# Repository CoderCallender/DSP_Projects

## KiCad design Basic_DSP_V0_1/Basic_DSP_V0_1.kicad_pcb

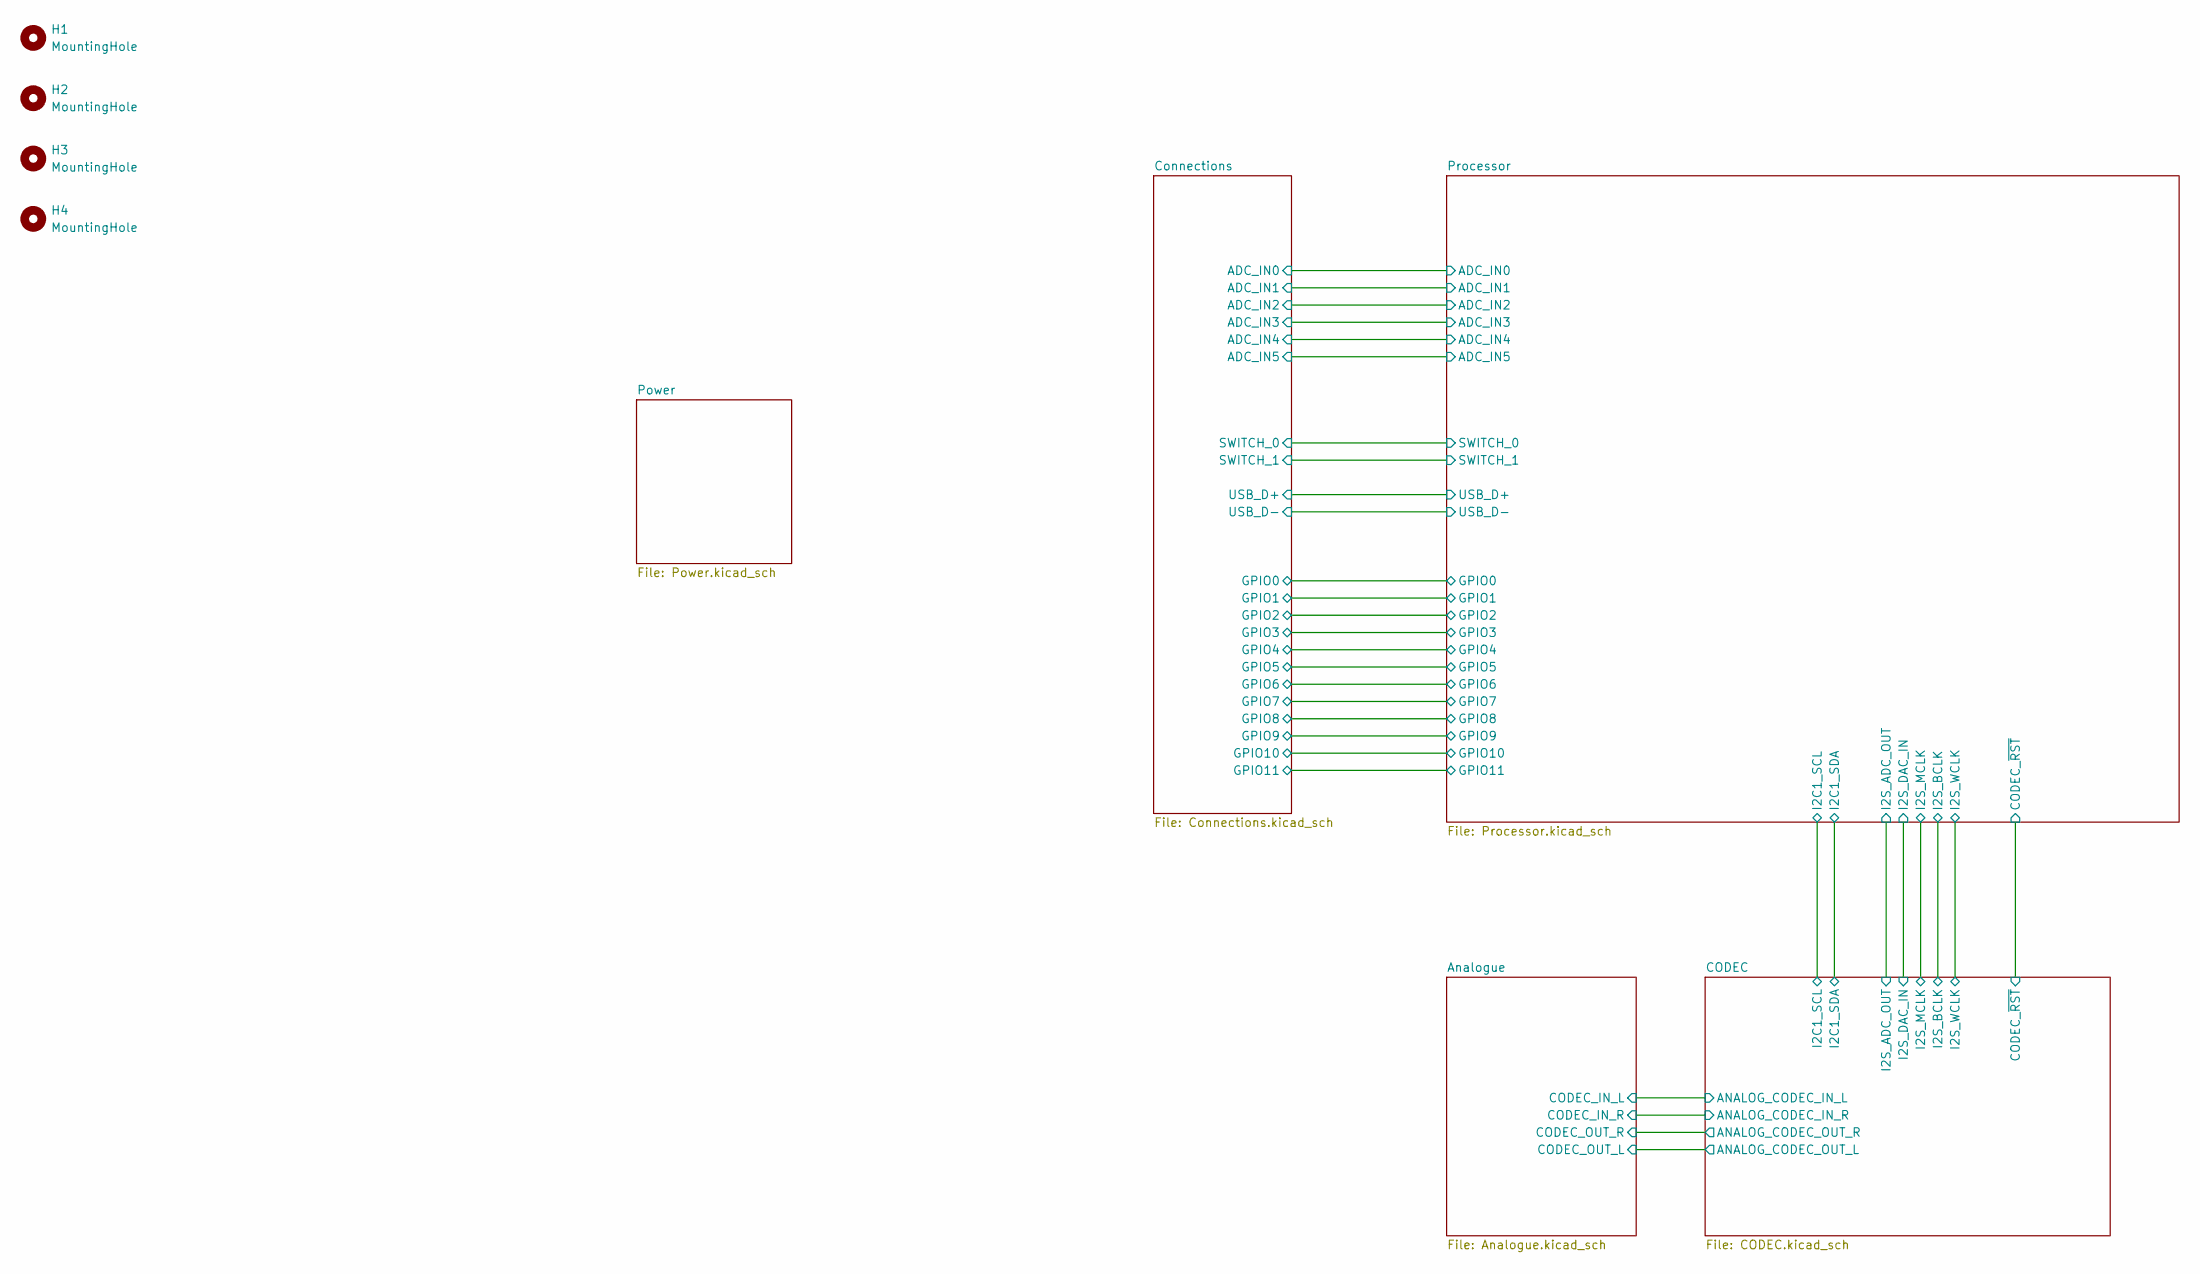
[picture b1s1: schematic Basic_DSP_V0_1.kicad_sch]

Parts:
H1, H2, H3, H4: MountingHole; MountingHole_3.2mm_M3_ISO7380_Pad

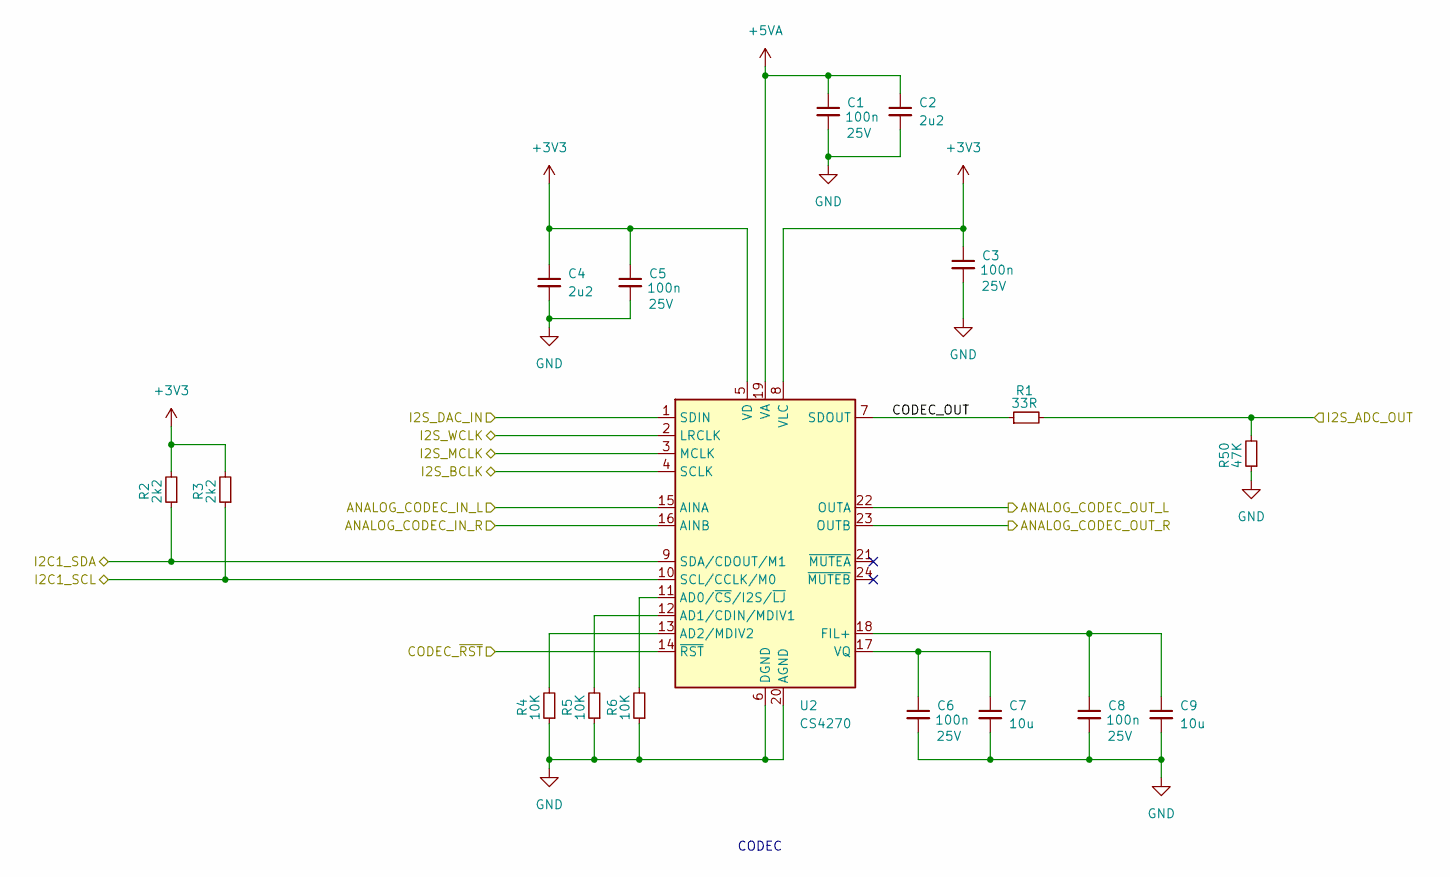
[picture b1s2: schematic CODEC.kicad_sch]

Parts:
C1, C3, C5, C6, C8: 100n; C_0603_1608Metric_Pad1.08x0.95mm_HandSolder; Voltage 25V; MPN 0603B104M250NT
C2, C4: 2u2; C_0603_1608Metric_Pad1.08x0.95mm_HandSolder; Voltage 25V; MPN 0603B225K250NT
C7, C9: 10u; C_0603_1608Metric_Pad1.08x0.95mm_HandSolder; Voltage 25V; MPN CL10A106MA8NRNC
R1: 33R; R_0603_1608Metric_Pad0.98x0.95mm_HandSolder; MPN WR06X33R0FTL
R2, R3: 2k2; R_0603_1608Metric_Pad0.98x0.95mm_HandSolder; MPN 0603WAF2201T5E
R4, R5, R6: 10K; R_0603_1608Metric_Pad0.98x0.95mm_HandSolder; MPN 0603WAF1002T5E
R50: 47K; R_0603_1608Metric_Pad0.98x0.95mm_HandSolder; MPN RC0603FR-0747KL
U2: CS4270; TSSOP-24_4.4x7.8mm_P0.65mm; MPN CS4270-CZZR

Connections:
+3V3: C3.1, C4.1, C5.1, R2.2, R3.2, U2.5 (VD), U2.8 (VLC); also elsewhere on the board
+5VA: C1.1, C2.1, U2.19 (VA); also elsewhere on the board
/Analogue/CODEC_IN_L: U2.15 (AINA); also elsewhere on the board
/Analogue/CODEC_IN_R: U2.16 (AINB); also elsewhere on the board
/Analogue/CODEC_OUT_L: U2.22 (OUTA); also elsewhere on the board
/Analogue/CODEC_OUT_R: U2.23 (OUTB); also elsewhere on the board
/CODEC/CODEC_OUT: R1.1, U2.7 (SDOUT)
/CODEC/CODEC_~RST: U2.14 (~RST); also elsewhere on the board
/CODEC/I2C1_SCL: R3.1, U2.10 (SCL/CCLK/M0); also elsewhere on the board
/CODEC/I2C1_SDA: R2.1, U2.9 (SDA/CDOUT/M1); also elsewhere on the board
/CODEC/I2S_ADC_OUT: R1.2, R50.2; also elsewhere on the board
/CODEC/I2S_BCLK: U2.4 (SCLK); also elsewhere on the board
/CODEC/I2S_DAC_IN: U2.1 (SDIN); also elsewhere on the board
/CODEC/I2S_MCLK: U2.3 (MCLK); also elsewhere on the board
/CODEC/I2S_WCLK: U2.2 (LRCLK); also elsewhere on the board
GND: C1.2, C2.2, C3.2, C4.2, C5.2, C6.2, C7.2, C8.2, C9.2, R4.1, R5.1, R6.1, R50.1, U2.6 (DGND), U2.20 (AGND); also elsewhere on the board
unnamed: R6.2, U2.11 (AD0/~CS/I2S/~LJ)
unnamed: R5.2, U2.12 (AD1/CDIN/MDIV1)
unnamed: R4.2, U2.13 (AD2/MDIV2)
unnamed: C8.1, C9.1, U2.18 (FIL+)
unnamed: C6.1, C7.1, U2.17 (VQ)

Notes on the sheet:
CODEC

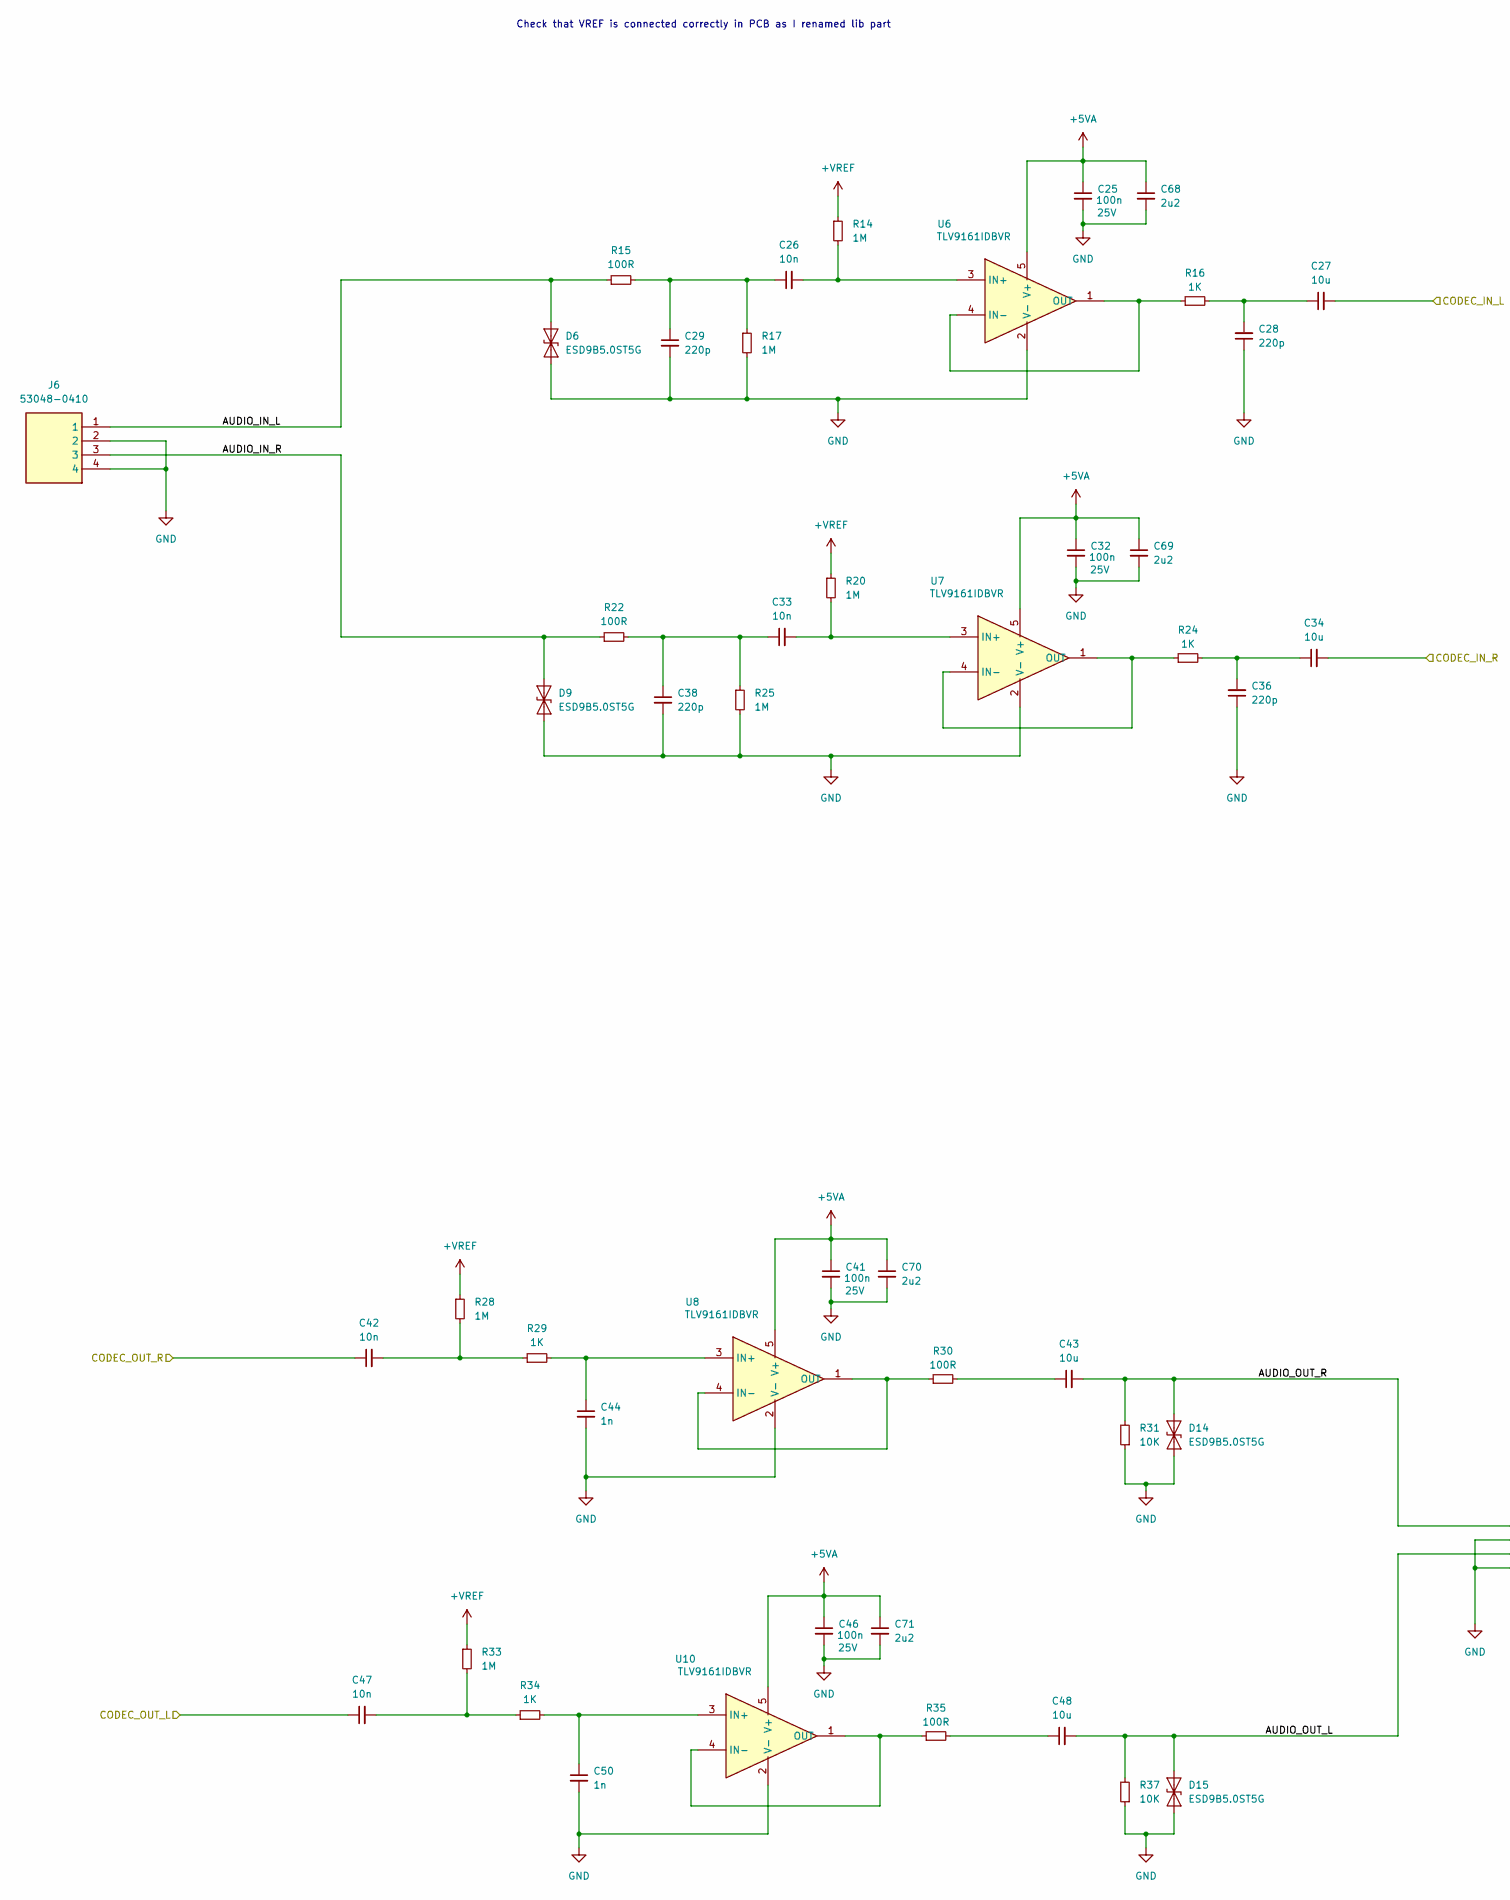
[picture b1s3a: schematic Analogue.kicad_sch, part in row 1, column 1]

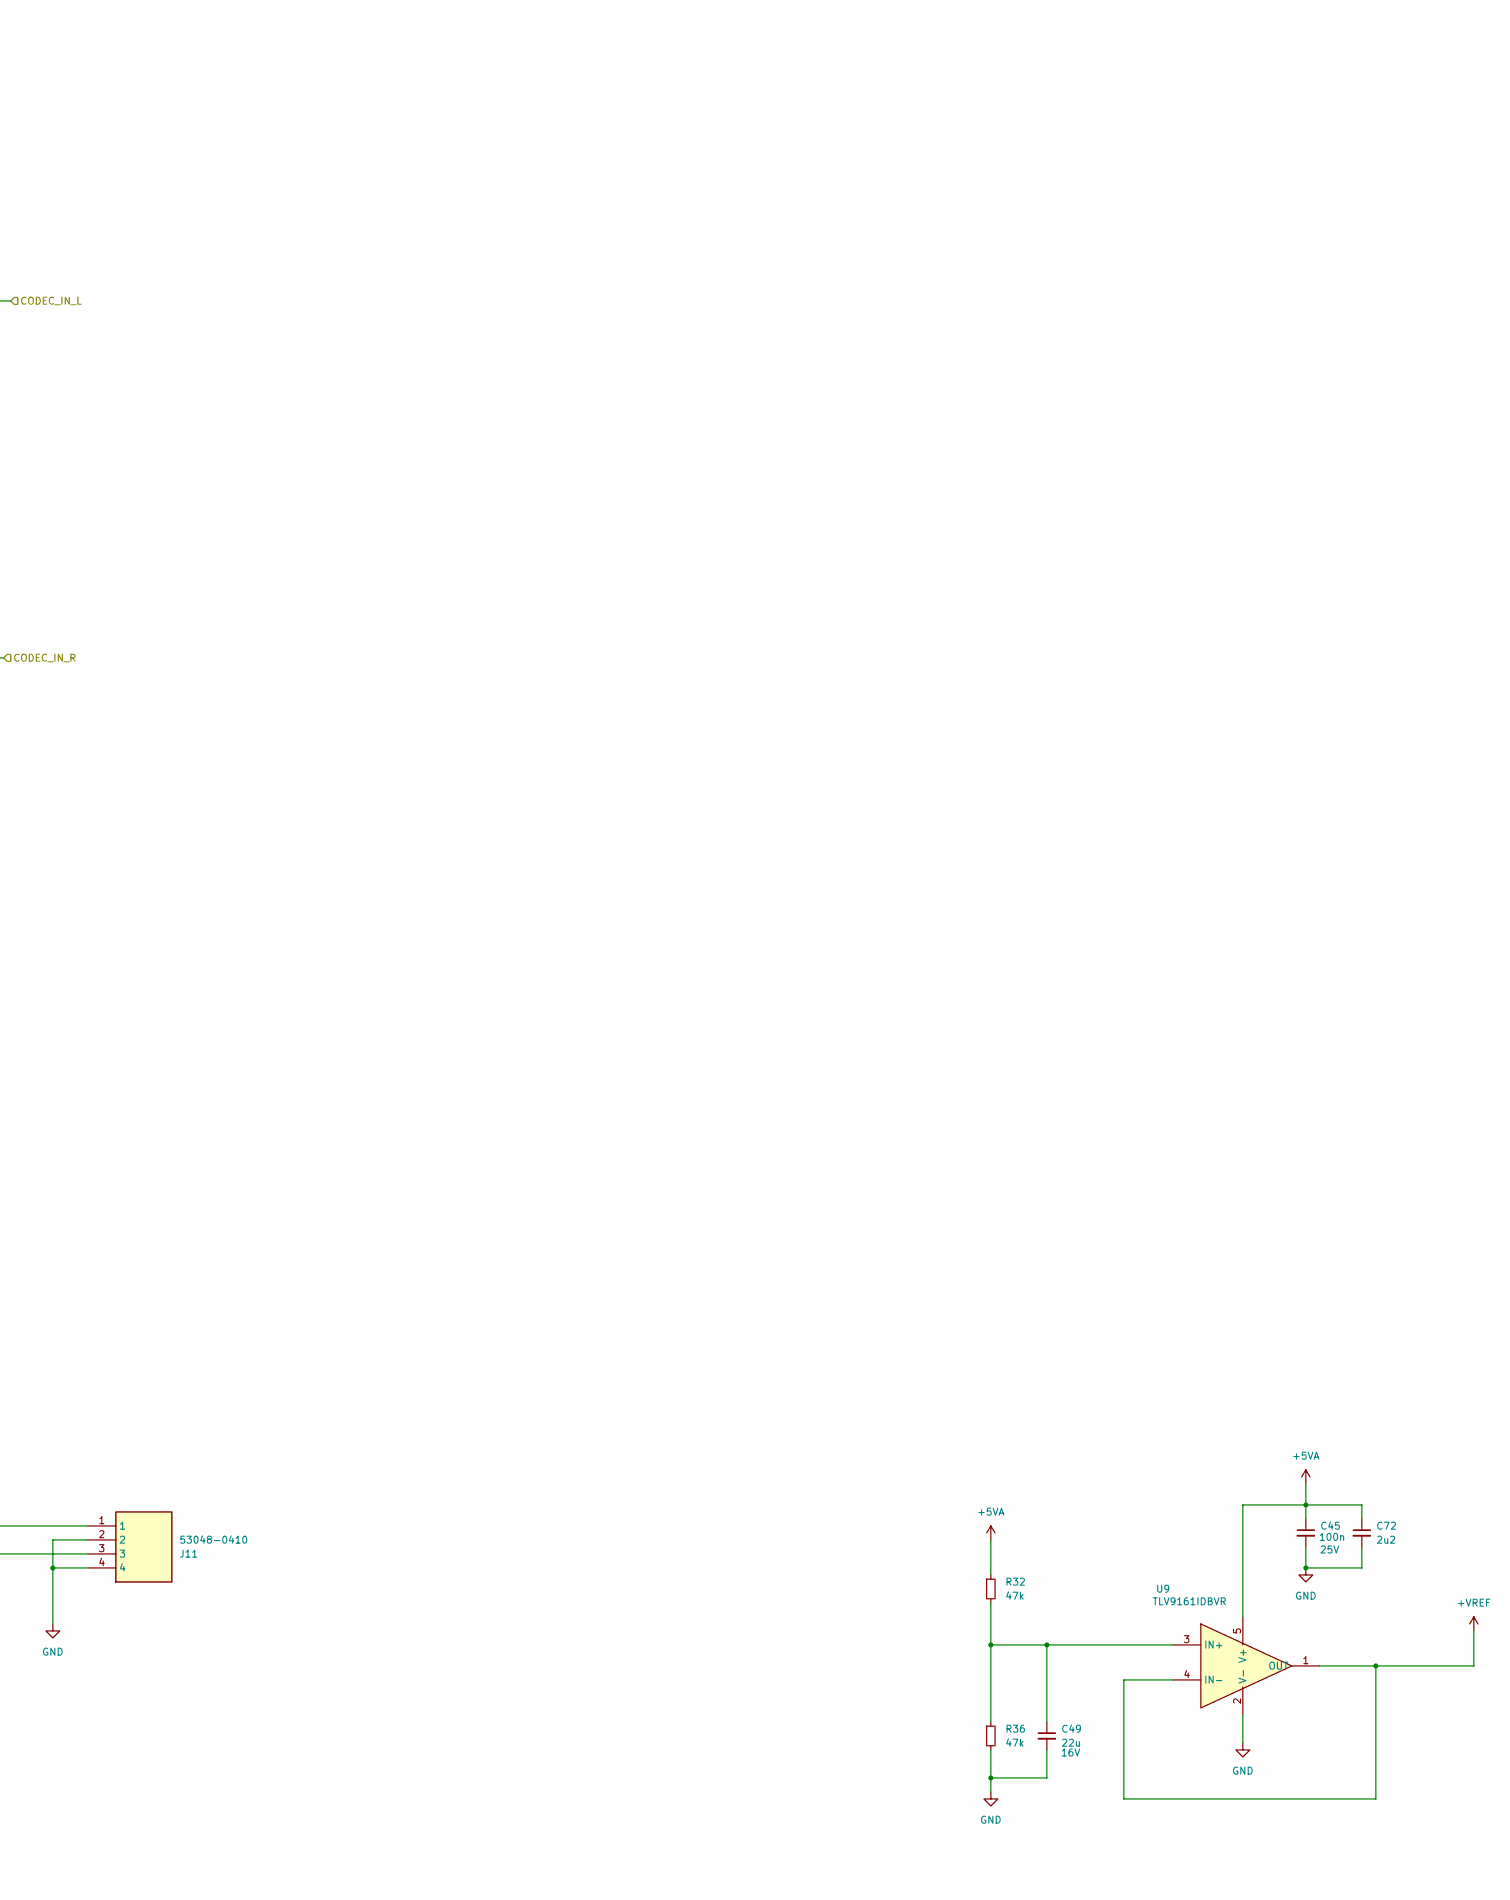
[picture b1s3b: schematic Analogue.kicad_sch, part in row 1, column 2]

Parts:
C25, C32, C41, C45, C46: 100n; C_0603_1608Metric_Pad1.08x0.95mm_HandSolder; Voltage 25V; MPN 0603B104M250NT
C26, C33, C42, C47: 10n; C_0603_1608Metric_Pad1.08x0.95mm_HandSolder; MPN CGA3E2X8R2A103KT0Y0H
C27, C34, C43, C48: 10u; C_0603_1608Metric_Pad1.08x0.95mm_HandSolder; Voltage 16V; MPN CL10A106MA8NRNC
C28, C29, C36, C38: 220p; C_0603_1608Metric_Pad1.08x0.95mm_HandSolder; MPN 0603N221J500CT
C44, C50: 1n; C_0603_1608Metric_Pad1.08x0.95mm_HandSolder; MPN GCJ188R71H102KA01D
C49: 22u; C_0603_1608Metric_Pad1.08x0.95mm_HandSolder; Voltage 16V; MPN CGA0603X5R226M160JT
C68, C69, C70, C71, C72: 2u2; C_0603_1608Metric_Pad1.08x0.95mm_HandSolder; Voltage 25V; MPN 0603B225K250NT
D6, D9, D14, D15: ESD9B5.0ST5G; D_SOD-923; MPN ESD9B5.0ST5G
J6, J11: 53048-0410; 530480410; Mouser Part Number 538-53048-0410
R14, R17, R20, R25, R28, R33: 1M; R_0603_1608Metric_Pad0.98x0.95mm_HandSolder; MPN 0603WAF1004T5E
R15, R22, R30, R35: 100R; R_0603_1608Metric_Pad0.98x0.95mm_HandSolder; MPN RC0603FR-07100RL
R16, R24, R29, R34: 1K; R_0603_1608Metric_Pad0.98x0.95mm_HandSolder; MPN 0603WAJ0102T5E
R31, R37: 10K; R_0603_1608Metric_Pad0.98x0.95mm_HandSolder; MPN 0603WAF1002T5E
R32, R36: 47k; R_0603_1608Metric_Pad0.98x0.95mm_HandSolder; MPN RC0603FR-0747KL
U6, U7, U8, U9, U10: TLV9161IDBVR; SOT95P280X145-5N; Mouser Part Number 595-TLV9161IDBVR

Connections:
+5VA: C25.1, C32.1, C41.1, C45.1, C46.1, C68.1, C69.1, C70.1, C71.1, C72.1, R32.1, U6.5 (V+), U7.5 (V+), U8.5 (V+), U9.5 (V+), U10.5 (V+); also elsewhere on the board
+VREF: R14.1, R20.1, R28.1, R33.1, U9.1 (OUT), U9.4 (IN-)
/Analogue/AUDIO_IN_L: D6.2 (A2), J6.1, R15.1
/Analogue/AUDIO_IN_R: D9.2 (A2), J6.3, R22.1
/Analogue/AUDIO_OUT_L: C48.2, D15.2 (A2), J11.3, R37.2
/Analogue/AUDIO_OUT_R: C43.2, D14.2 (A2), J11.1, R31.2
/Analogue/CODEC_IN_L: C27.2; also elsewhere on the board
/Analogue/CODEC_IN_R: C34.2; also elsewhere on the board
/Analogue/CODEC_OUT_L: C47.1; also elsewhere on the board
/Analogue/CODEC_OUT_R: C42.1; also elsewhere on the board
GND: C25.2, C28.1, C29.2, C32.2, C36.1, C38.2, C41.2, C44.2, C45.2, C46.2, C49.2, C50.2, C68.2, C69.2, C70.2, C71.2, C72.2, D6.1 (A1), D9.1 (A1), D14.1 (A1), D15.1 (A1), J6.2, J6.4, J11.2, J11.4, R17.2, R25.2, R31.1, R36.2, R37.1, U6.2 (V-), U7.2 (V-), U8.2 (V-), U9.2 (V-), U10.2 (V-); also elsewhere on the board
unnamed: C26.1, C29.1, R15.2, R17.1
unnamed: C27.1, C28.2, R16.2
unnamed: C33.1, C38.1, R22.2, R25.1
unnamed: C34.1, C36.2, R24.2
unnamed: C42.2, R28.2, R29.1
unnamed: C43.1, R30.2
unnamed: C47.2, R33.2, R34.1
unnamed: C48.1, R35.2
unnamed: C26.2, R14.2, U6.3 (IN+)
unnamed: R16.1, U6.1 (OUT), U6.4 (IN-)
unnamed: C33.2, R20.2, U7.3 (IN+)
unnamed: R24.1, U7.1 (OUT), U7.4 (IN-)
unnamed: C44.1, R29.2, U8.3 (IN+)
unnamed: R30.1, U8.1 (OUT), U8.4 (IN-)
unnamed: C49.1, R32.2, R36.1, U9.3 (IN+)
unnamed: C50.1, R34.2, U10.3 (IN+)
unnamed: R35.1, U10.1 (OUT), U10.4 (IN-)

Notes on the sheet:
Check that VREF is connected correctly in PCB as I renamed lib part

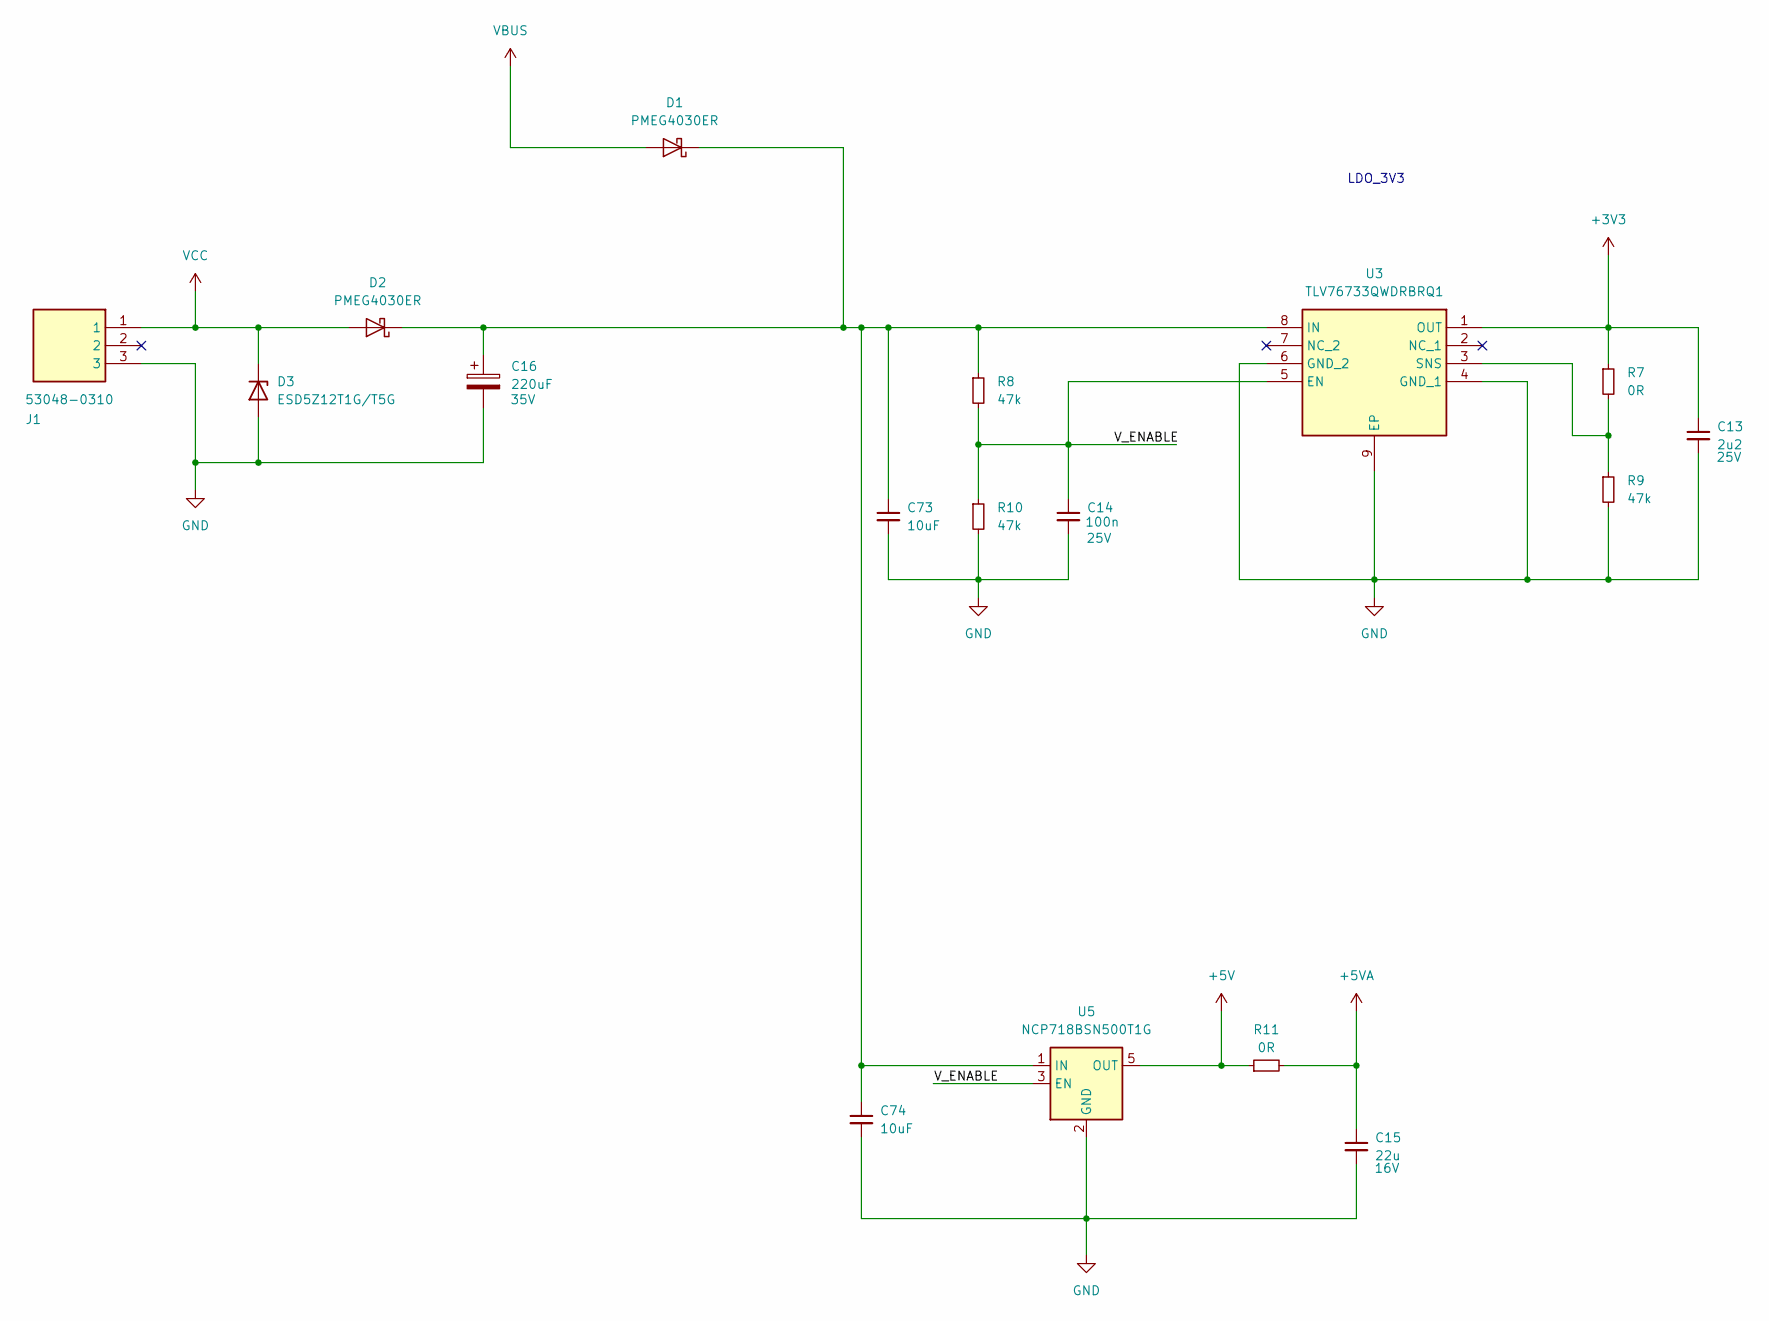
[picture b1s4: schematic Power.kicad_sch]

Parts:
C13: 2u2; C_0603_1608Metric_Pad1.08x0.95mm_HandSolder; Voltage 25V; MPN 0603B225K250NT
C14: 100n; C_0603_1608Metric_Pad1.08x0.95mm_HandSolder; Voltage 25V; MPN 0603B104M250NT
C15: 22u; C_0603_1608Metric_Pad1.08x0.95mm_HandSolder; Voltage 16V; MPN CGA0603X5R226M160JT
C16: 220uF; CP_Elec_8x10.5; Voltage 35V; MPN CK1V221M-CRF10
C73, C74: 10uF; C_0603_1608Metric; MPN CL10A106MA8NRNC
D1, D2: PMEG4030ER; Nexperia_CFP3_SOD-123W; MPN PMEG4030ER
D3: ESD5Z12T1G/T5G; D_SOD-523; Voltage 12V; MPN ESD5Z12T1G
J1: 53048-0310; SHDRRA3W35P0X125_1X3_550X550X350P; Mouser Part Number 538-53048-0310
R7: 0R; R_0603_1608Metric_Pad0.98x0.95mm_HandSolder; MPN 0603WAF0000T5E
R8, R9, R10: 47k; R_0603_1608Metric_Pad0.98x0.95mm_HandSolder; MPN RC0603FR-0747KL
R11: 0R; R_0603_1608Metric_Pad0.98x0.95mm_HandSolder; MPN 0603WAF100JT5E
U3: TLV76733QWDRBRQ1; SON65P300X300X100-9N-D; Mouser Part Number 595-TLV76733QWDRBRQ1
U5: NCP718BSN500T1G; SOT-23-5; MPN NCP718BSN500T1G

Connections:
+3V3: C13.1, R7.1, U3.1 (OUT); also elsewhere on the board
+5V: R11.1, U5.5 (OUT); also elsewhere on the board
+5VA: C15.1, R11.2; also elsewhere on the board
/Power/V_ENABLE: C14.1, R8.2, R10.1, U3.5 (EN), U5.3 (EN)
GND: C13.2, C14.2, C15.2, C16.2, C73.2, C74.2, D3.2 (A), J1.3, R9.2, R10.2, U3.4 (GND_1), U3.6 (GND_2), U3.9 (EP), U5.2 (GND); also elsewhere on the board
unnamed: C16.1, C73.1, C74.1, D1.1 (K), D2.1 (K), R8.1, U3.8 (IN), U5.1 (IN)
unnamed: R7.2, R9.1, U3.3 (SNS)
VBUS: D1.2 (A); also elsewhere on the board
VCC: D2.2 (A), D3.1 (K), J1.1

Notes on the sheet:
LDO_3V3

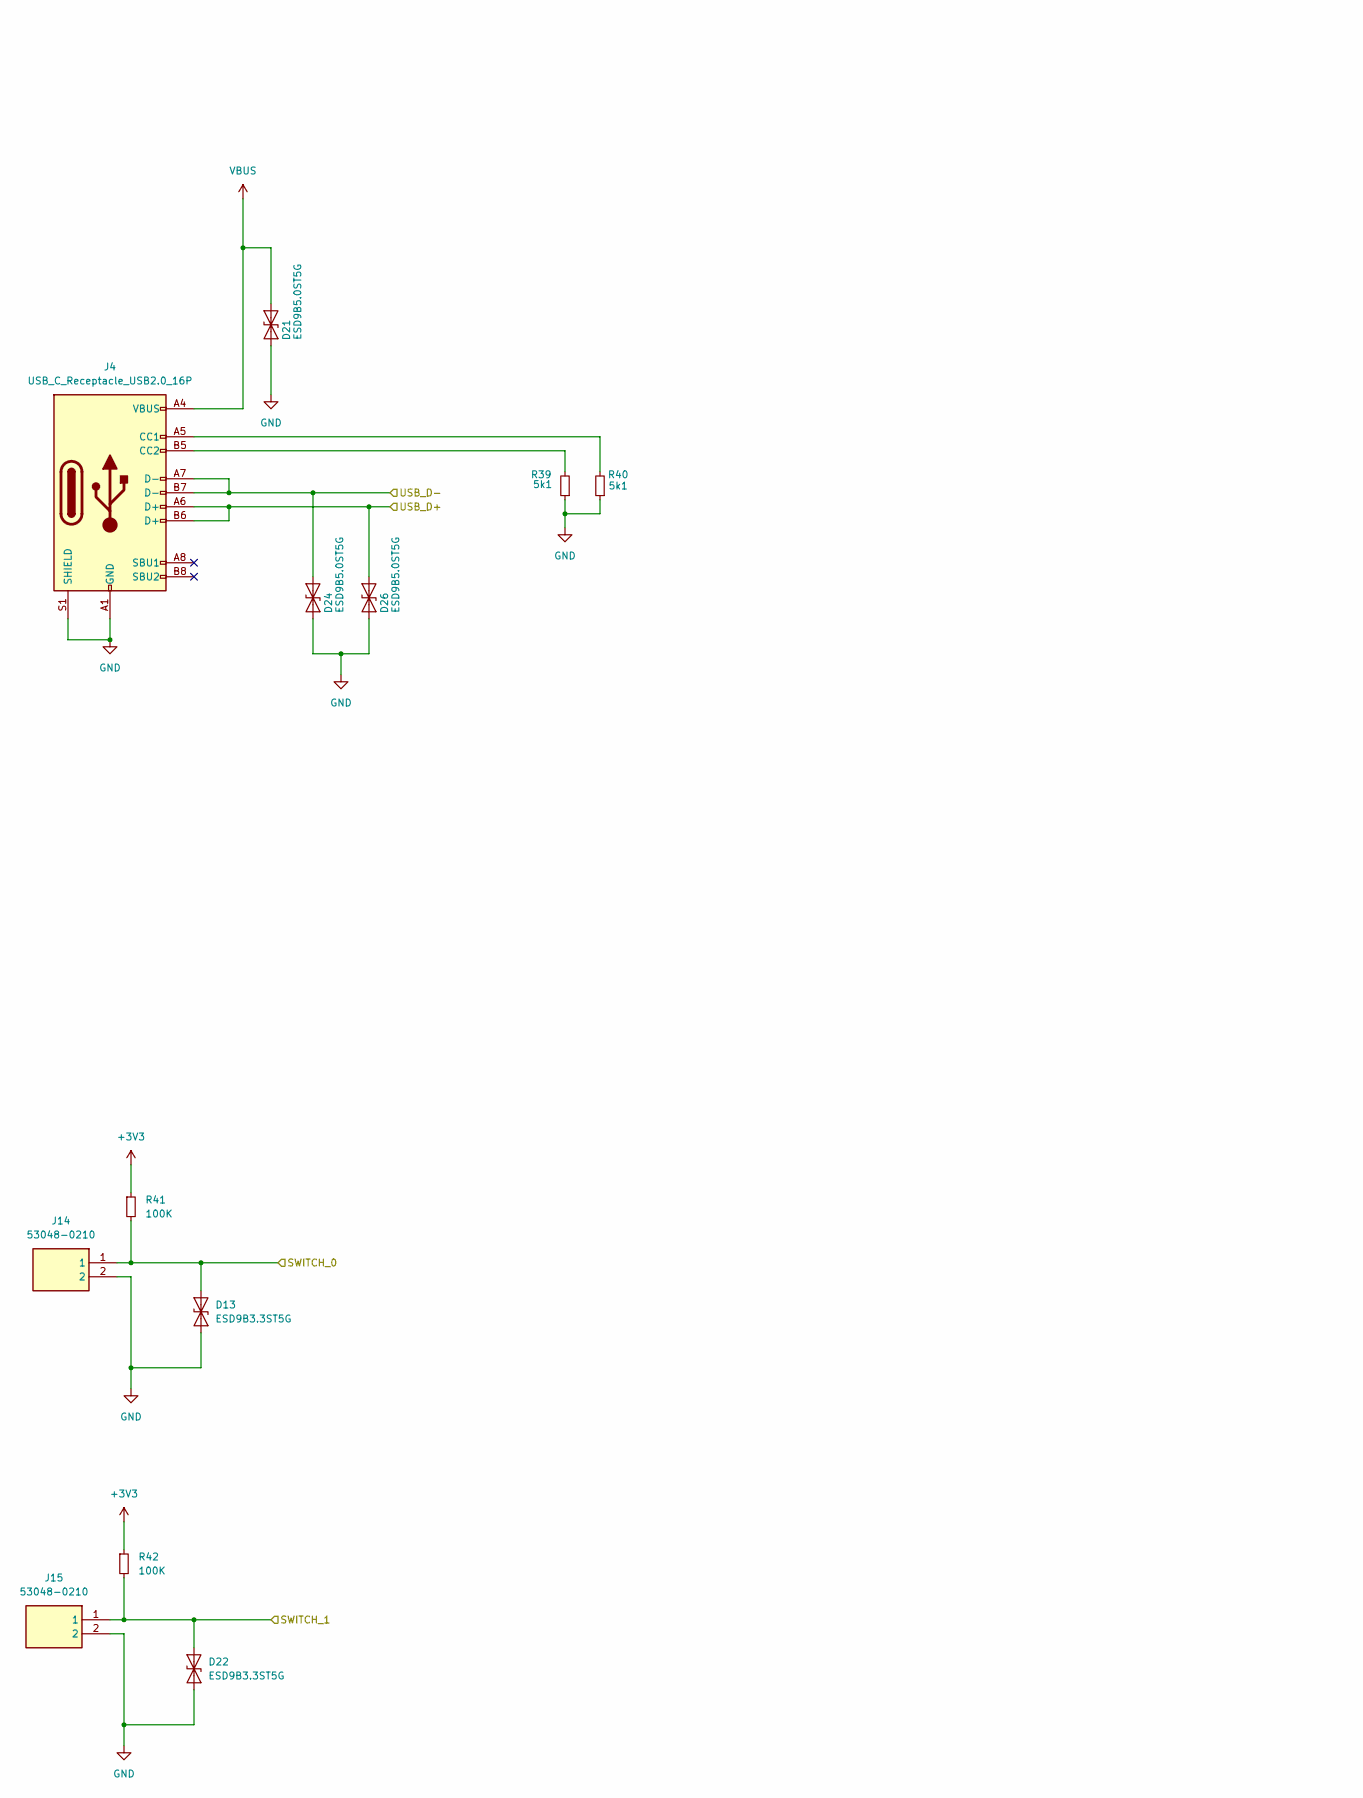
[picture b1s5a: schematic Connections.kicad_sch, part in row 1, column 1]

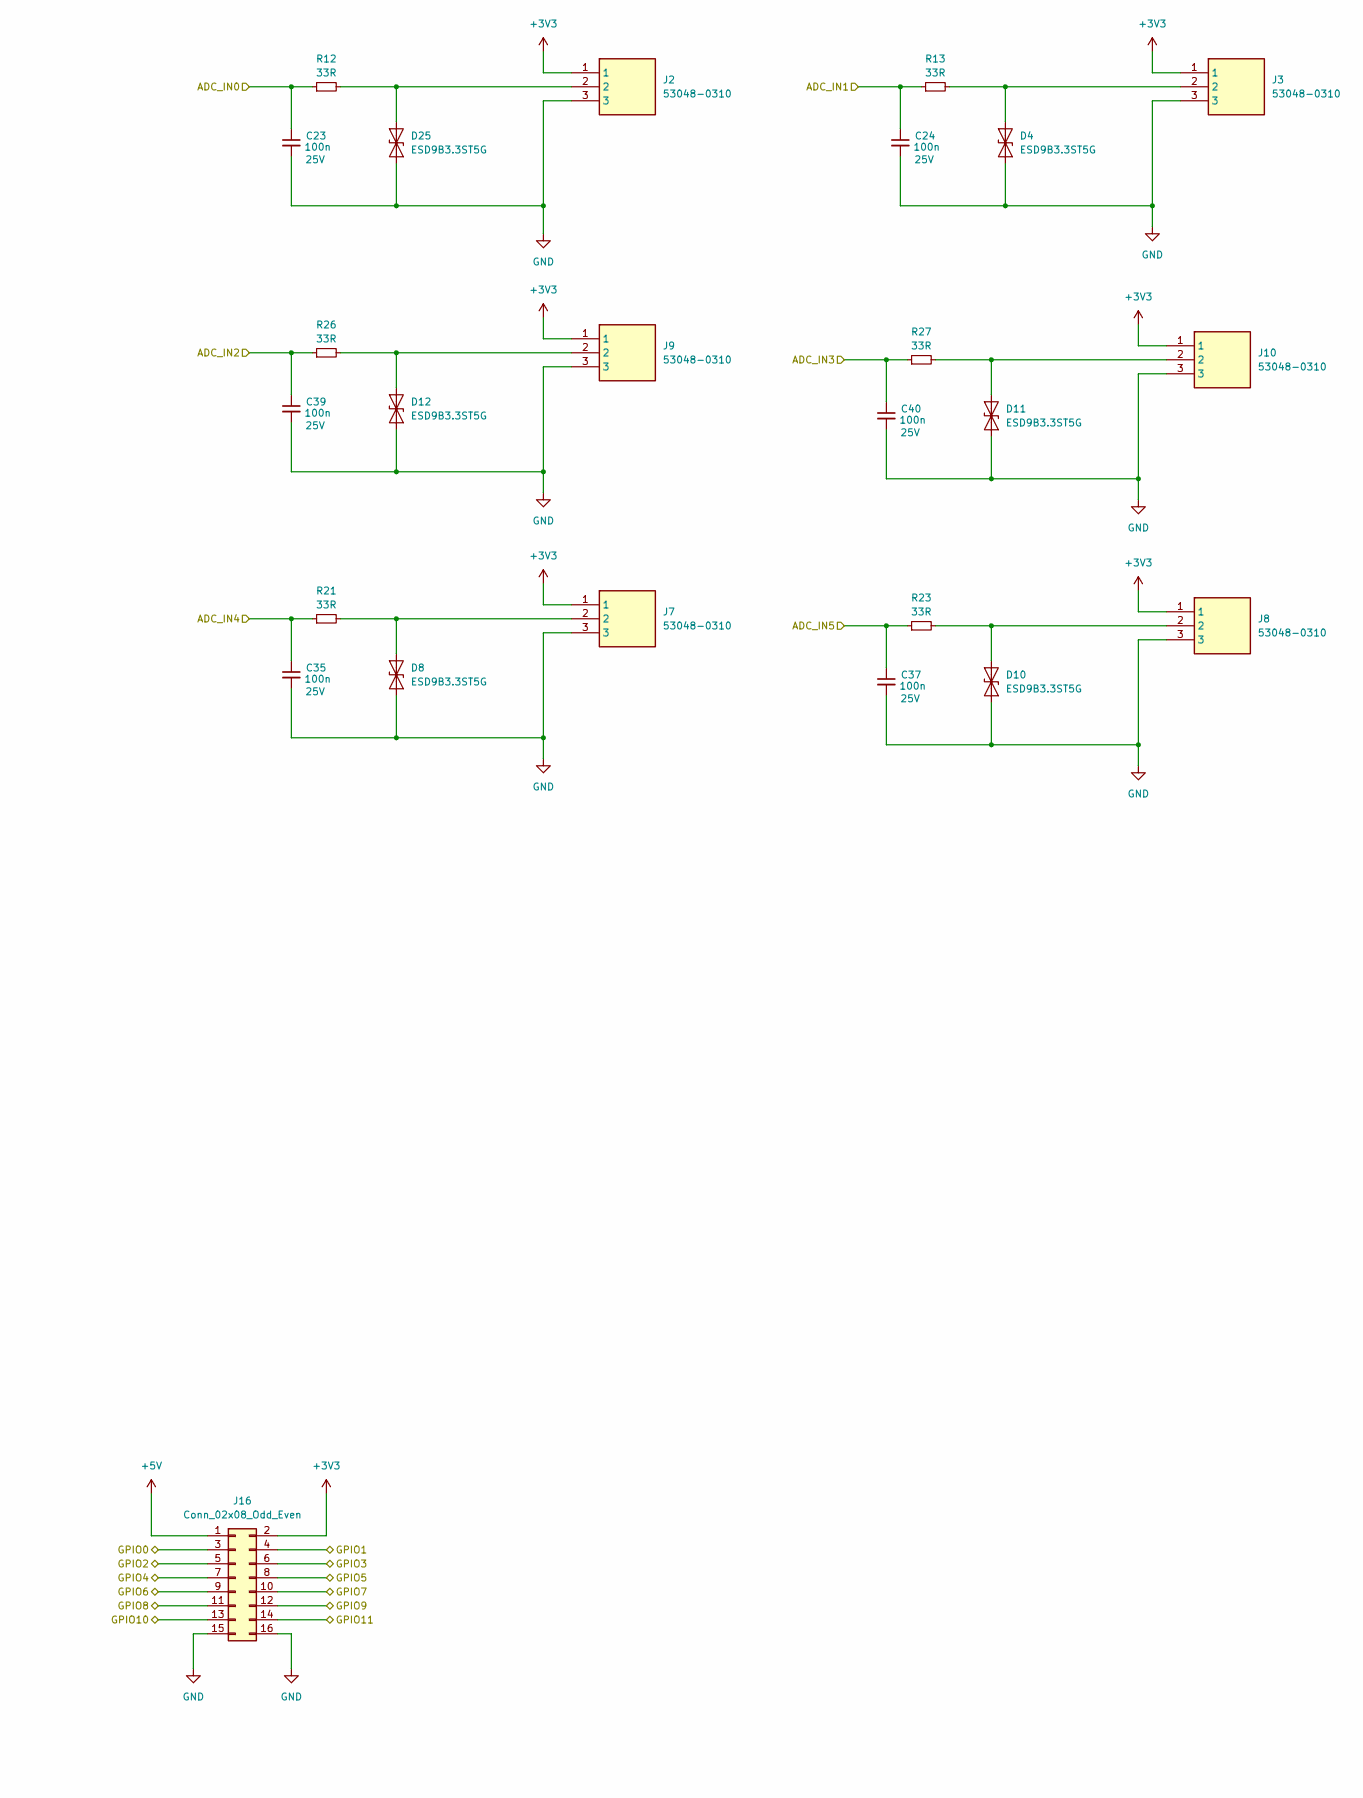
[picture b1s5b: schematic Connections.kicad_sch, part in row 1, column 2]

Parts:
C23, C24, C35, C37, C39, C40: 100n; C_0603_1608Metric_Pad1.08x0.95mm_HandSolder; Voltage 25V; MPN 0603B104M250NT
D4, D8, D10, D11, D12, D13, D22, D25: ESD9B3.3ST5G; D_SOD-923; MPN ESD9B3.3ST5G
D21, D24, D26: ESD9B5.0ST5G; D_SOD-923; MPN ESD9B5.0ST5G
J2, J3, J7, J8, J9, J10: 53048-0310; SHDRRA3W35P0X125_1X3_550X550X350P; Mouser Part Number 538-53048-0310
J4: USB_C_Receptacle_USB2.0_16P; USB_C_Receptacle_GCT_USB4110
J14, J15: 53048-0210; SHDRRA2W35P0X125_1X2_425X550X350P; Mouser Part Number 538-53048-0210
J16: Conn_02x08_Odd_Even; PinSocket_2x08_P2.54mm_Vertical
R12, R13, R21, R23, R26, R27: 33R; R_0603_1608Metric_Pad0.98x0.95mm_HandSolder; MPN WR06X33R0FTL
R39, R40: 5k1; R_0603_1608Metric_Pad0.98x0.95mm_HandSolder; MPN 0603WAF5101T5E
R41, R42: 100K; R_0603_1608Metric_Pad0.98x0.95mm_HandSolder; MPN RC0603FR-07100KL

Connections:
+3V3: J2.1, J3.1, J7.1, J8.1, J9.1, J10.1, J16.2, R41.1, R42.1; also elsewhere on the board
+5V: J16.1; also elsewhere on the board
/Connections/ADC_IN0: C23.1, R12.1; also elsewhere on the board
/Connections/ADC_IN1: C24.1, R13.1; also elsewhere on the board
/Connections/ADC_IN2: C39.1, R26.1; also elsewhere on the board
/Connections/ADC_IN3: C40.1, R27.1; also elsewhere on the board
/Connections/ADC_IN4: C35.1, R21.1; also elsewhere on the board
/Connections/ADC_IN5: C37.1, R23.1; also elsewhere on the board
/Connections/GPIO0: J16.3; also elsewhere on the board
/Connections/GPIO1: J16.4; also elsewhere on the board
/Connections/GPIO2: J16.5; also elsewhere on the board
/Connections/GPIO3: J16.6; also elsewhere on the board
/Connections/GPIO4: J16.7; also elsewhere on the board
/Connections/GPIO5: J16.8; also elsewhere on the board
/Connections/GPIO6: J16.9; also elsewhere on the board
/Connections/GPIO7: J16.10; also elsewhere on the board
/Connections/GPIO8: J16.11; also elsewhere on the board
/Connections/GPIO9: J16.12; also elsewhere on the board
/Connections/GPIO10: J16.13; also elsewhere on the board
/Connections/GPIO11: J16.14; also elsewhere on the board
/Connections/SWITCH_0: D13.2 (A2), J14.1, R41.2; also elsewhere on the board
/Connections/SWITCH_1: D22.2 (A2), J15.1, R42.2; also elsewhere on the board
/Connections/USB_D+: D26.2 (A2), J4.A6 (D+), J4.B6 (D+); also elsewhere on the board
/Connections/USB_D-: D24.2 (A2), J4.A7 (D-), J4.B7 (D-); also elsewhere on the board
GND: C23.2, C24.2, C35.2, C37.2, C39.2, C40.2, D4.1 (A1), D8.1 (A1), D10.1 (A1), D11.1 (A1), D12.1 (A1), D13.1 (A1), D21.1 (A1), D22.1 (A1), D24.1 (A1), D25.1 (A1), D26.1 (A1), J2.3, J3.3, J4.A1 (GND), J4.A12 (GND), J4.B1 (GND), J4.B12 (GND), J4.S1 (SHIELD), J7.3, J8.3, J9.3, J10.3, J14.2, J15.2, J16.15, J16.16, R39.1, R40.1; also elsewhere on the board
unnamed: D4.2 (A2), J3.2, R13.2
unnamed: D8.2 (A2), J7.2, R21.2
unnamed: D10.2 (A2), J8.2, R23.2
unnamed: D11.2 (A2), J10.2, R27.2
unnamed: D12.2 (A2), J9.2, R26.2
unnamed: D25.2 (A2), J2.2, R12.2
unnamed: J4.A5 (CC1), R40.2
unnamed: J4.B5 (CC2), R39.2
VBUS: D21.2 (A2), J4.A4 (VBUS), J4.A9 (VBUS), J4.B4 (VBUS), J4.B9 (VBUS); also elsewhere on the board
